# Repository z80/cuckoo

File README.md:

# Micropython Board
A convenient to work with implementation. It is not a minimalistic design, 
it has a full size USB-B socket, 16Mb of external SPI memory. The board is driven by STM32 microcontroller STM32F405RGT6.

All min arrays have extensive ground shielding and even neighbor pins have minimal crosstalk.

The layout is designed closely following the rules made by Hans Rosenberg, shared in his correct PCB layout tutorial videos.

# Audio Board
This is an extension for the micropython board. This audio board has a D-class on-chip power amplifier with analog input.

It has a step up 5V switching converter to ensure the audio driver is at 5V.

Also, it has a motion detector (PYR sensor) redinc circuit.

Lastly, it has a single driver circuit for an analog servo motor.

The intended usage of the board in Helloween props. The micropython board can be extended with this audio board to produce speech, detect when people approach, perform physical movements.

# Override Board
This board provides several analog and digital isolated IO channels. The intended use is to override analog turning axes in the Dial Sense Playstation 5 controller and force it to use external intertial aiming signal so that instead of being a torture device, it makes the Dual Sense to be pleasant to use.

# Servo Scull prop
A talking scull themed as Warhammer 40k Servo Scull by Adeptus Mechanicus.

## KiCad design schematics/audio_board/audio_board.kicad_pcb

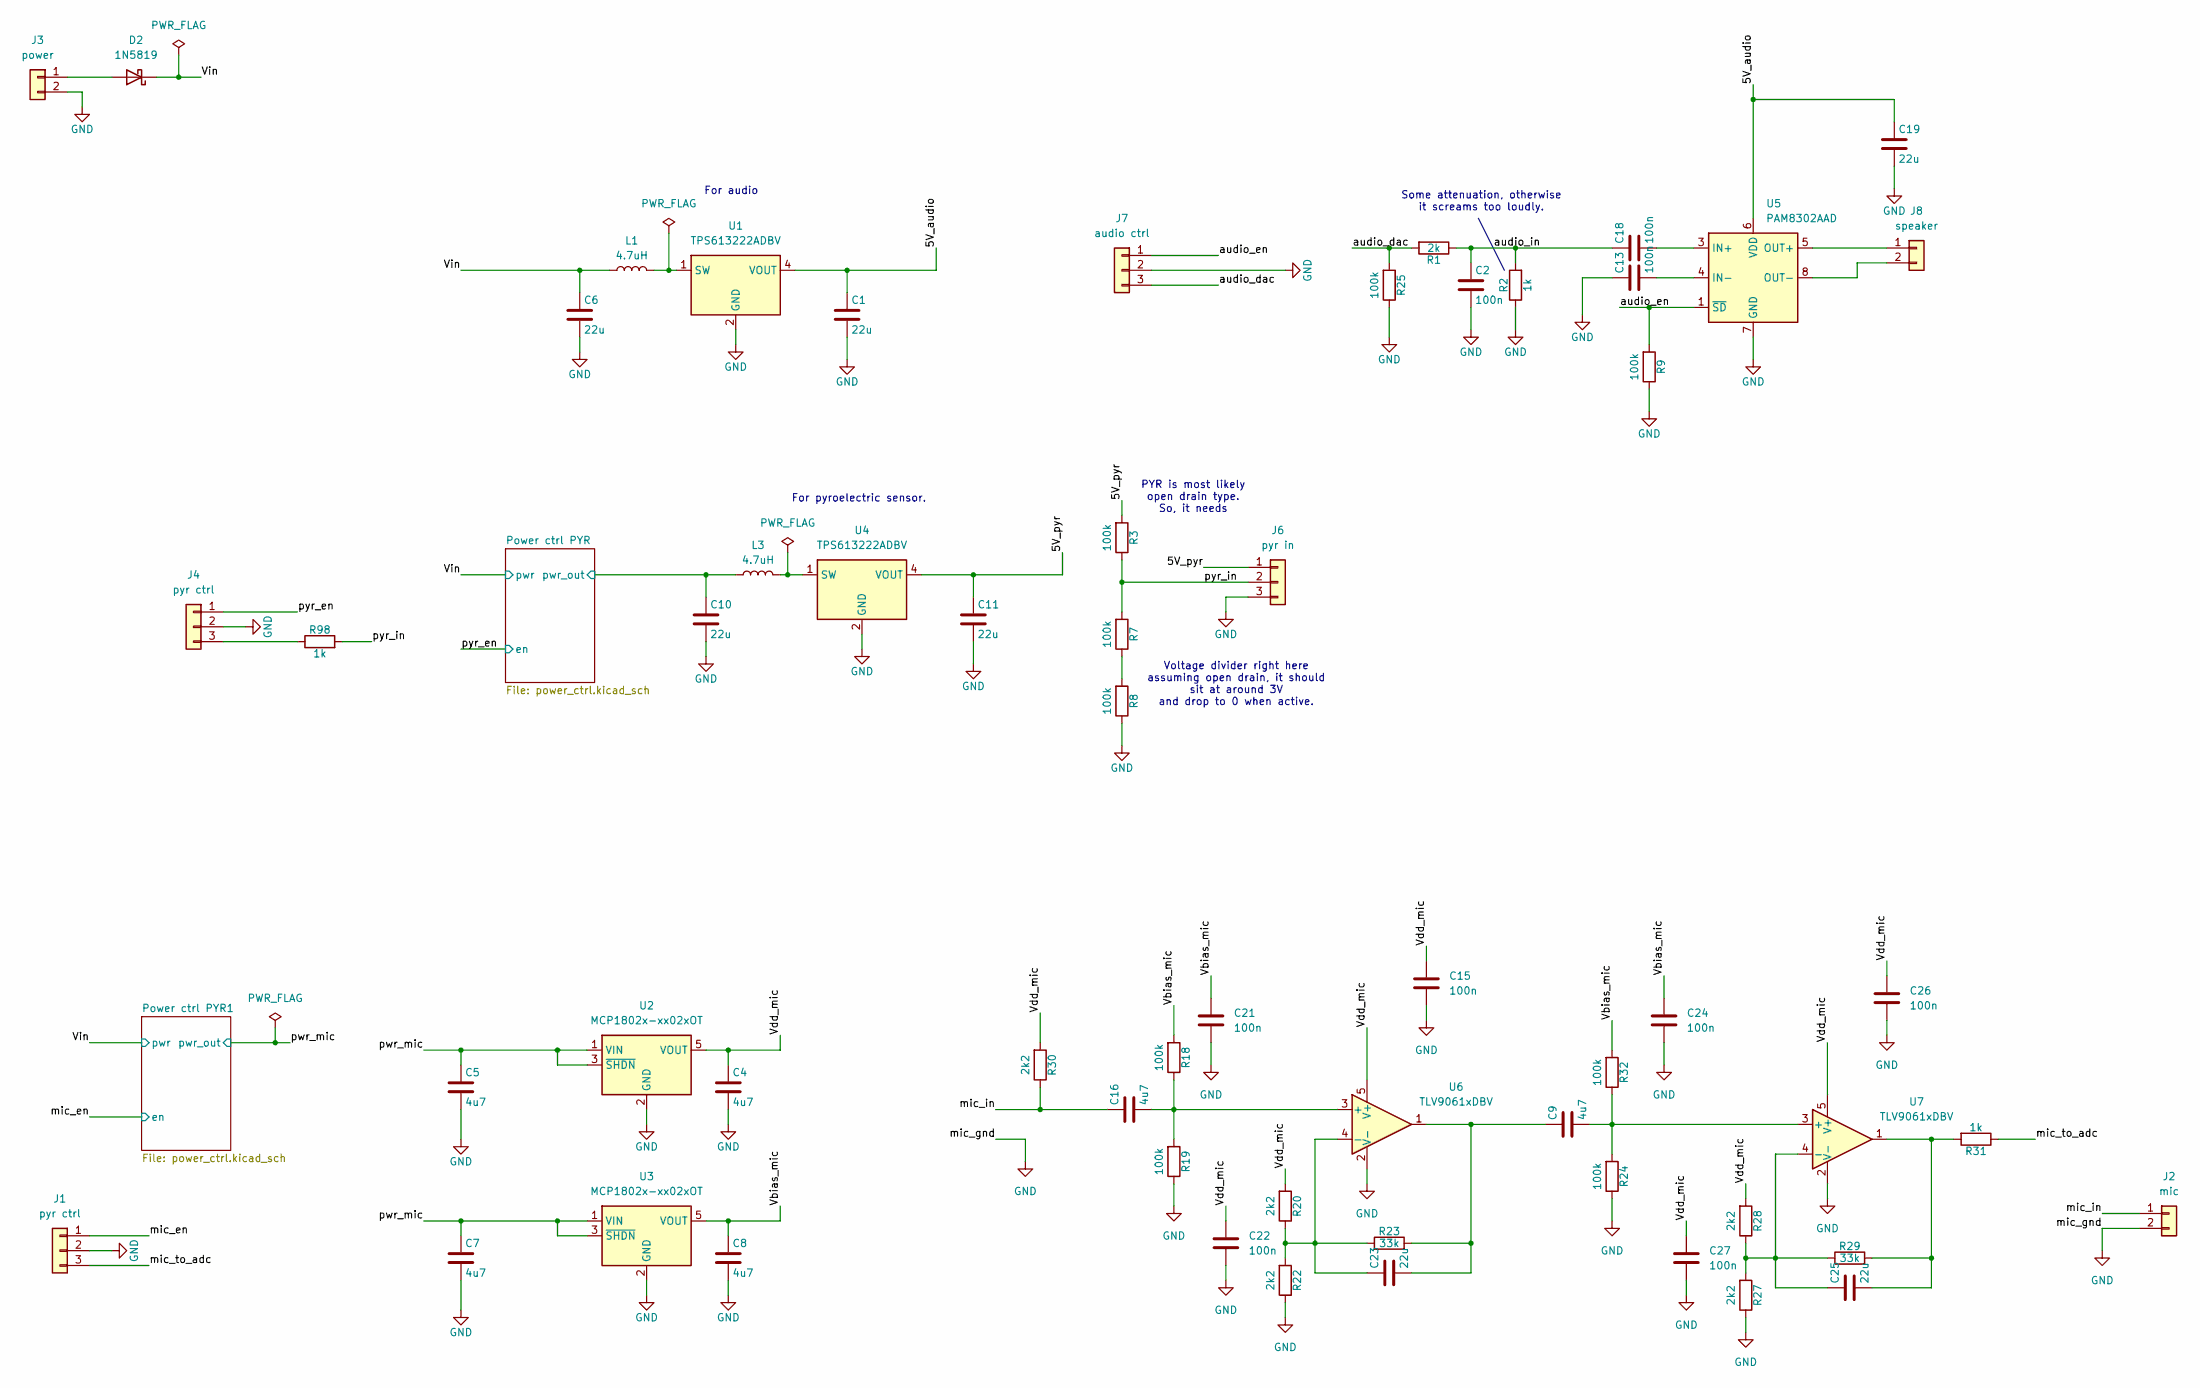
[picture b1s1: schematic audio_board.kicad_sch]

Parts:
C1, C6, C10, C11, C19, C23, C25: 22u; C_0603_1608Metric_Pad1.08x0.95mm_HandSolder
C2, C13, C18: 100n; C_0603_1608Metric_Pad1.08x0.95mm_HandSolder
C4, C5, C7, C8, C9, C16: 4u7; C_0603_1608Metric
C15, C21, C22, C24, C26, C27: 100n; C_0603_1608Metric
D2: 1N5819; D_DO-41_SOD81_P7.62mm_Horizontal
J1, J4: pyr ctrl; PinSocket_1x03_P2.54mm_Vertical
J2: mic; PinSocket_1x02_P2.54mm_Vertical
J3: power; PinSocket_1x02_P2.54mm_Vertical
J6: pyr in; PinSocket_1x03_P2.54mm_Vertical
J7: audio ctrl; PinSocket_1x03_P2.54mm_Vertical
J8: speaker; PinSocket_1x02_P2.54mm_Vertical
L1, L3: 4.7uH; L_1008_2520Metric
R1: 2k; C_0603_1608Metric_Pad1.08x0.95mm_HandSolder
R2, R31, R98: 1k; C_0603_1608Metric_Pad1.08x0.95mm_HandSolder
R3, R7, R8, R9, R18, R19, R24, R25, R32: 100k; R_0603_1608Metric_Pad0.98x0.95mm_HandSolder
R20, R22, R27, R28, R30: 2k2; R_0603_1608Metric_Pad0.98x0.95mm_HandSolder
R23, R29: 33k; C_0603_1608Metric_Pad1.08x0.95mm_HandSolder
U1, U4: TPS613222ADBV; SOT-23-5
U2, U3: MCP1802x-xx02xOT; SOT-23-5
U5: PAM8302AAD; MSOP-8_3x3mm_P0.65mm
U6, U7: TLV9061xDBV; SOT-23-5

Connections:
/5V_audio: C1.1, C19.1, U1.4 (VOUT), U5.6 (VDD)
/5V_pyr: C11.1, J6.1, R3.2, U4.4 (VOUT)
/Power ctrl PYR/pwr_out: C10.1, L3.1; also elsewhere on the board
/Vbias_mic: C8.1, C21.1, C24.1, R18.2, R32.2, U3.5 (VOUT)
/Vdd_mic: C4.1, C15.1, C22.1, C26.1, C27.1, R20.2, R28.2, R30.2, U2.5 (VOUT), U6.5 (V+), U7.5 (V+)
/Vin: C6.1, D2.1 (K), L1.1; also elsewhere on the board
/audio_dac: J7.3, R1.2, R25.2
/audio_en: J7.1, R9.2, U5.1 (~SD)
/audio_in: C2.1, C18.1, R1.1, R2.2
/mic_en: J1.1; also elsewhere on the board
/mic_in: C16.1, J2.1, R30.1
/mic_to_adc: J1.3, R31.1
/pwr_mic: C5.1, C7.1, U2.1 (VIN), U2.3 (~SHDN), U3.1 (VIN), U3.3 (~SHDN); also elsewhere on the board
/pyr_en: J4.1; also elsewhere on the board
/pyr_in: J6.2, R3.1, R7.2, R98.2
GND: C1.2, C2.2, C4.2, C5.2, C6.2, C7.2, C8.2, C10.2, C11.2, C13.1, C15.2, C19.2, C21.2, C22.2, C24.2, C26.2, C27.2, J1.2, J2.2, J3.2, J4.2, J6.3, J7.2, R2.1, R8.1, R9.1, R19.1, R22.1, R24.1, R25.1, R27.1, U1.2 (GND), U2.2 (GND), U3.2 (GND), U4.2 (GND), U5.7 (GND), U6.2 (V-), U7.2 (V-); also elsewhere on the board
unnamed: C9.1, C23.2, R23.2, U6.1
unnamed: C25.2, R29.2, R31.2, U7.1
unnamed: D2.2 (A), J3.1
unnamed: J4.3, R98.1
unnamed: J8.1, U5.5 (OUT+)
unnamed: J8.2, U5.8 (OUT-)
unnamed: R7.1, R8.2
unnamed: L1.2, U1.1 (SW)
unnamed: L3.2, U4.1 (SW)
unnamed: C18.2, U5.3 (IN+)
unnamed: C13.2, U5.4 (IN-)
unnamed: C16.2, R18.1, R19.2, U6.3 (+)
unnamed: C23.1, R20.1, R22.2, R23.1, U6.4 (-)
unnamed: C9.2, R24.2, R32.1, U7.3 (+)
unnamed: C25.1, R27.2, R28.1, R29.1, U7.4 (-)

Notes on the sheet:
For pyroelectric sensor.
PYR is most likely open drain type. So, it needs
For audio
Voltage divider right here assuming open drain, it should sit at around 3V and drop to 0 when active.
Some attenuation, otherwise it screams too loudly.

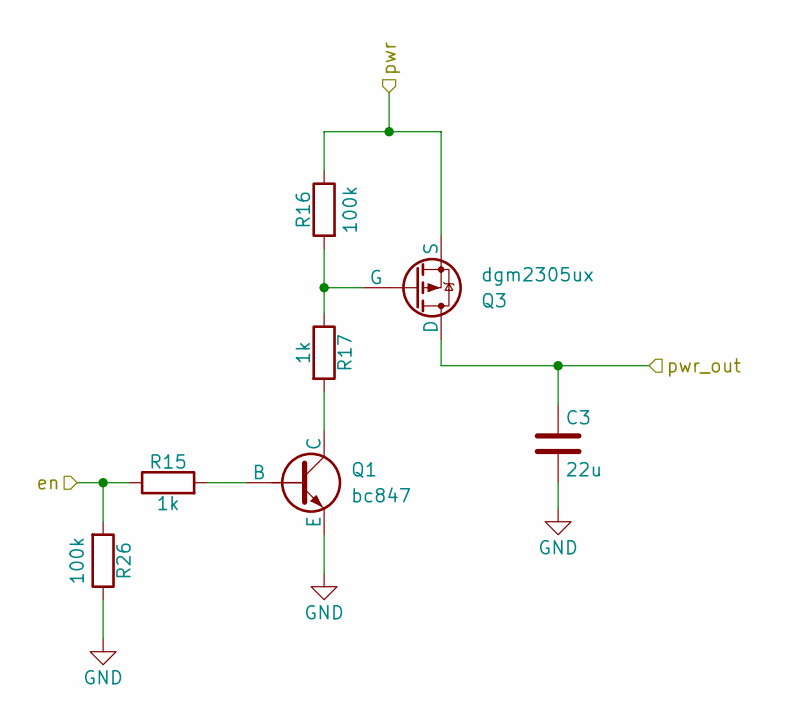
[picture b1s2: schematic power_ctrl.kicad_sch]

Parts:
C3: 22u; C_0603_1608Metric_Pad1.08x0.95mm_HandSolder
Q1: bc847; SOT-23
Q3: dgm2305ux; SOT-23
R15, R17: 1k; C_0603_1608Metric_Pad1.08x0.95mm_HandSolder
R16, R26: 100k; R_0603_1608Metric_Pad0.98x0.95mm_HandSolder

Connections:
/Vin: Q3.2 (S), R16.1; also elsewhere on the board
/mic_en: R15.1, R26.2; also elsewhere on the board
/pwr_mic: C3.1, Q3.3 (D); also elsewhere on the board
GND: C3.2, Q1.2 (E), R26.1; also elsewhere on the board
unnamed: Q1.1 (B), R15.2
unnamed: Q1.3 (C), R17.2
unnamed: Q3.1 (G), R16.2, R17.1

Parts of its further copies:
C14: 22u; C_0603_1608Metric_Pad1.08x0.95mm_HandSolder
Q2: bc847; SOT-23
Q7: dgm2305ux; SOT-23
R5, R11: 1k; C_0603_1608Metric_Pad1.08x0.95mm_HandSolder
R6, R33: 100k; R_0603_1608Metric_Pad0.98x0.95mm_HandSolder

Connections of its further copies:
/Power ctrl PYR/pwr_out: C14.1, Q7.3 (D); also elsewhere on the board
/Vin: Q7.2 (S), R6.1; also elsewhere on the board
/pyr_en: R5.1, R33.2; also elsewhere on the board
GND: C14.2, Q2.2 (E), R33.1; also elsewhere on the board
unnamed: Q2.1 (B), R5.2
unnamed: Q2.3 (C), R11.2
unnamed: Q7.1 (G), R6.2, R11.1

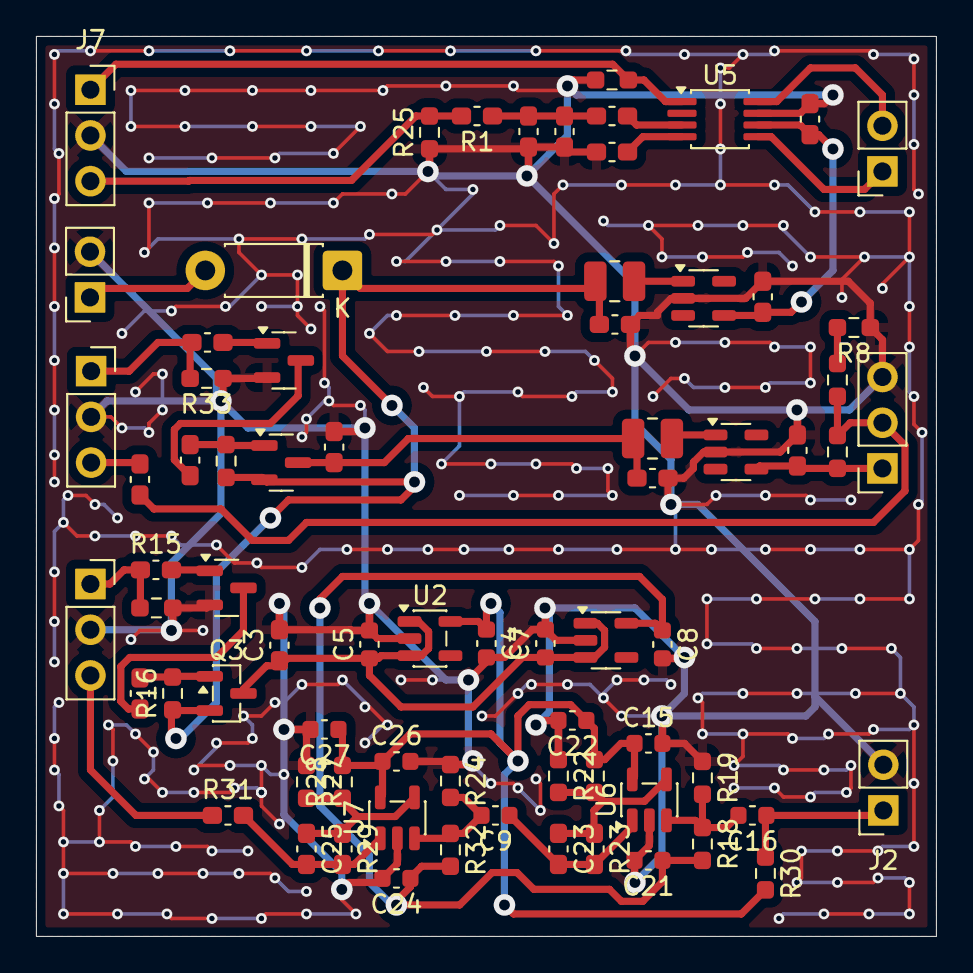
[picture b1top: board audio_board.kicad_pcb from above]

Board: 2 copper layers, 50.0 x 50.0 mm, 73 parts (0 on the bottom side), 37 nets.

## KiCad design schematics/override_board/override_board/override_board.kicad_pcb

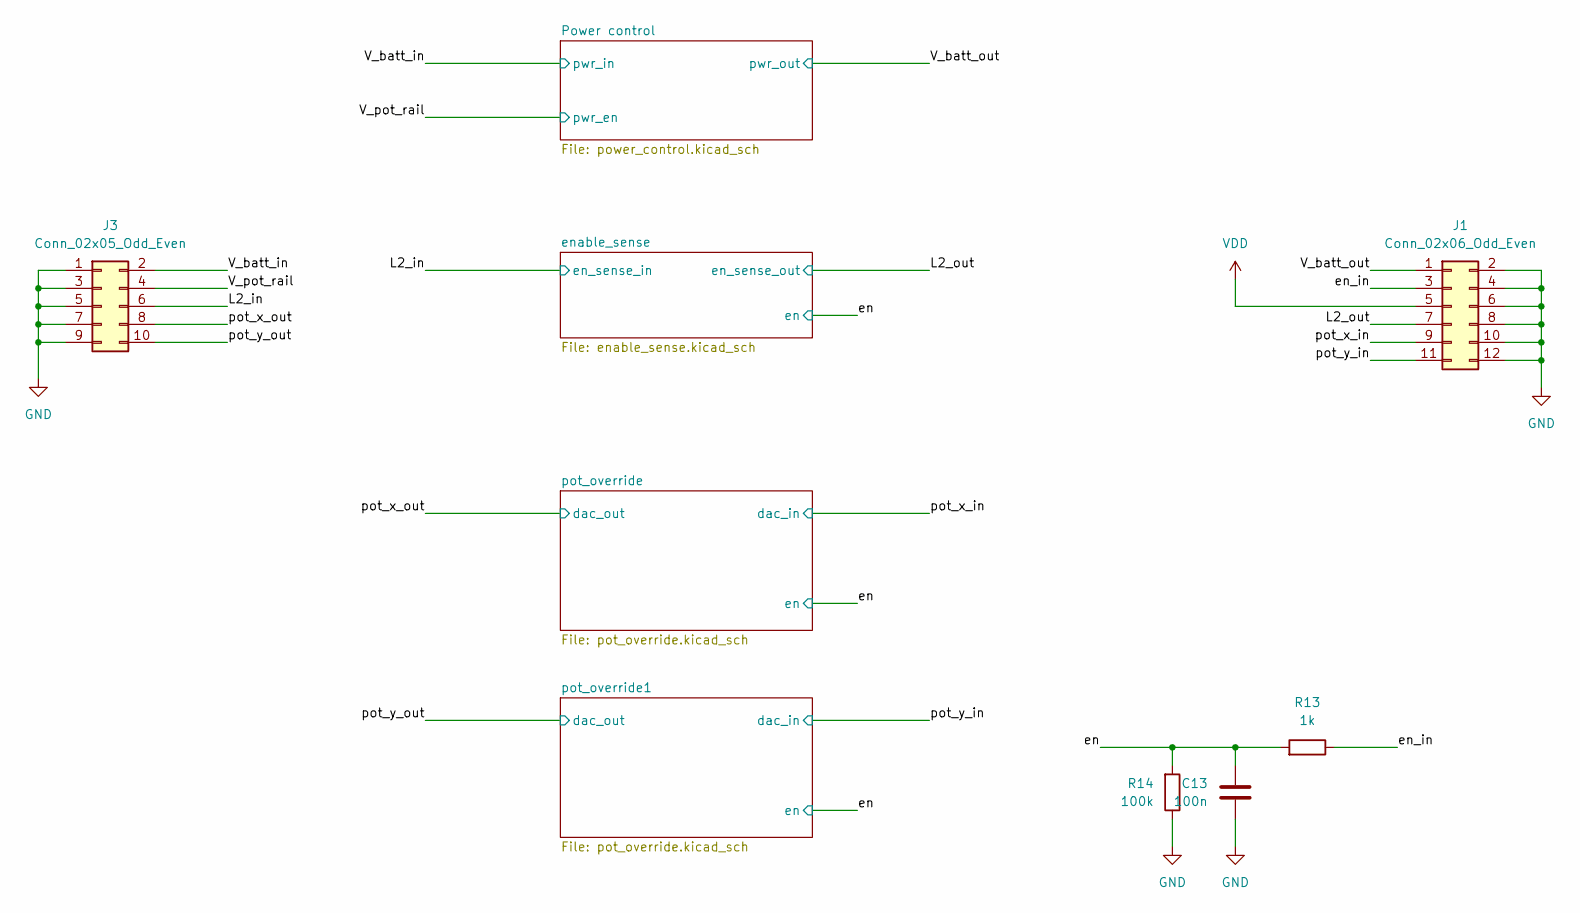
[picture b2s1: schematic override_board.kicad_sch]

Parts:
C13: 100n; C_0603_1608Metric
J1: Conn_02x06_Odd_Even; PinHeader_2x06_P2.54mm_Vertical
J3: Conn_02x05_Odd_Even; PinHeader_2x05_P2.54mm_Vertical
R13: 1k; R_0603_1608Metric
R14: 100k; R_0603_1608Metric

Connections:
/L2_in: J3.6; also elsewhere on the board
/L2_out: J1.7; also elsewhere on the board
/V_batt_in: J3.2; also elsewhere on the board
/V_batt_out: J1.1; also elsewhere on the board
/V_pot_rail: J3.4; also elsewhere on the board
/en: C13.1, R13.2, R14.2; also elsewhere on the board
/en_in: J1.3, R13.1
/pot_x_in: J1.9; also elsewhere on the board
/pot_x_out: J3.8; also elsewhere on the board
/pot_y_in: J1.11; also elsewhere on the board
/pot_y_out: J3.10; also elsewhere on the board
GND: C13.2, J1.2, J1.4, J1.6, J1.8, J1.10, J1.12, J3.1, J3.3, J3.5, J3.7, J3.9, R14.1; also elsewhere on the board
VDD: J1.5; also elsewhere on the board

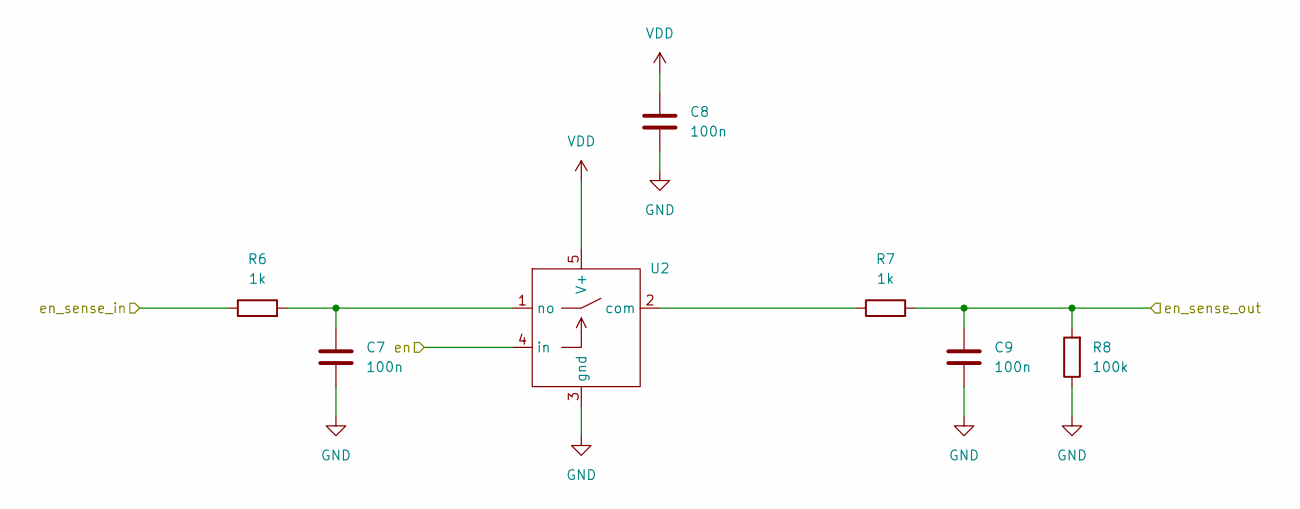
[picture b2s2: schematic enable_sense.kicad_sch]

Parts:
C7, C8, C9: 100n; C_0603_1608Metric
R6, R7: 1k; R_0603_1608Metric
R8: 100k; R_0603_1608Metric
U2: SOT-23-5

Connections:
/L2_in: R6.1; also elsewhere on the board
/L2_out: C9.1, R7.2, R8.2; also elsewhere on the board
/en: U2.4 (in); also elsewhere on the board
GND: C7.2, C8.2, C9.2, R8.1, U2.3 (gnd); also elsewhere on the board
unnamed: R7.1, U2.2 (com)
unnamed: C7.1, R6.2, U2.1 (no)
VDD: C8.1, U2.5 (V+); also elsewhere on the board

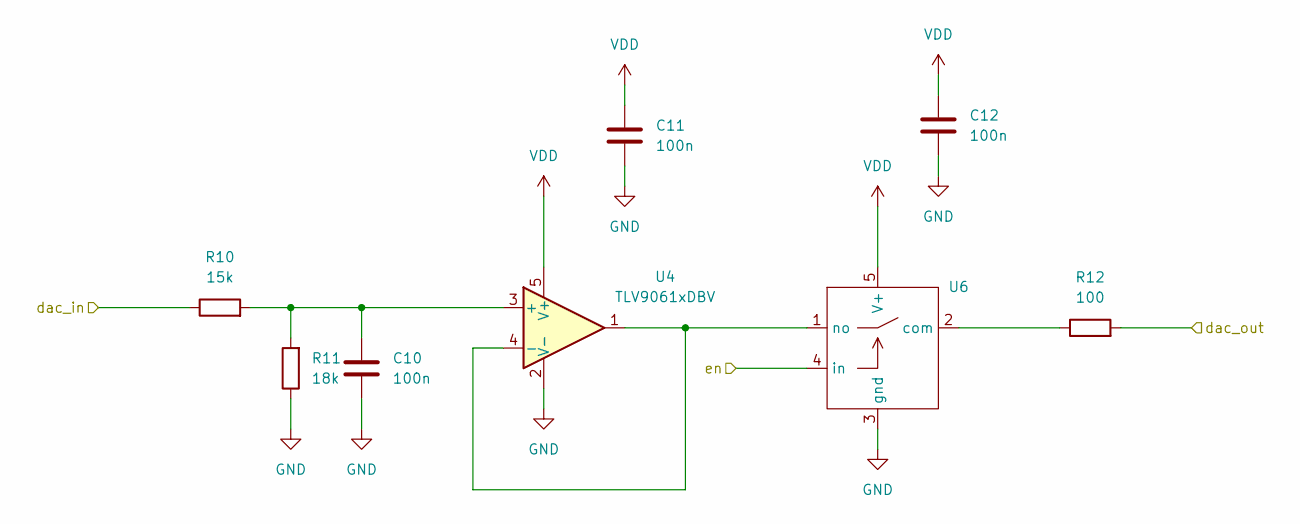
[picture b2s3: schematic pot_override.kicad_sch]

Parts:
C10, C11, C12: 100n; C_0603_1608Metric
R10: 15k; R_0603_1608Metric
R11: 18k; R_0603_1608Metric
R12: 100; R_0603_1608Metric
U4: TLV9061xDBV; SOT-23-5
U6: SOT-23-5

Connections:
/en: U6.4 (in); also elsewhere on the board
/pot_x_in: R10.1; also elsewhere on the board
/pot_x_out: R12.2; also elsewhere on the board
GND: C10.2, C11.2, C12.2, R11.1, U4.2 (V-), U6.3 (gnd); also elsewhere on the board
unnamed: C10.1, R10.2, R11.2, U4.3 (+)
unnamed: U4.1, U4.4 (-), U6.1 (no)
unnamed: R12.1, U6.2 (com)
VDD: C11.1, C12.1, U4.5 (V+), U6.5 (V+); also elsewhere on the board

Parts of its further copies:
C4, C5, C6: 100n; C_0603_1608Metric
R3: 15k; R_0603_1608Metric
R4: 18k; R_0603_1608Metric
R5: 100; R_0603_1608Metric
U3: TLV9061xDBV; SOT-23-5
U5: SOT-23-5

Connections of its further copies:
/en: U5.4 (in); also elsewhere on the board
/pot_y_in: R3.1; also elsewhere on the board
/pot_y_out: R5.2; also elsewhere on the board
GND: C4.2, C5.2, C6.2, R4.1, U3.2 (V-), U5.3 (gnd); also elsewhere on the board
unnamed: C4.1, R3.2, R4.2, U3.3 (+)
unnamed: U3.1, U3.4 (-), U5.1 (no)
unnamed: R5.1, U5.2 (com)
VDD: C5.1, C6.1, U3.5 (V+), U5.5 (V+); also elsewhere on the board

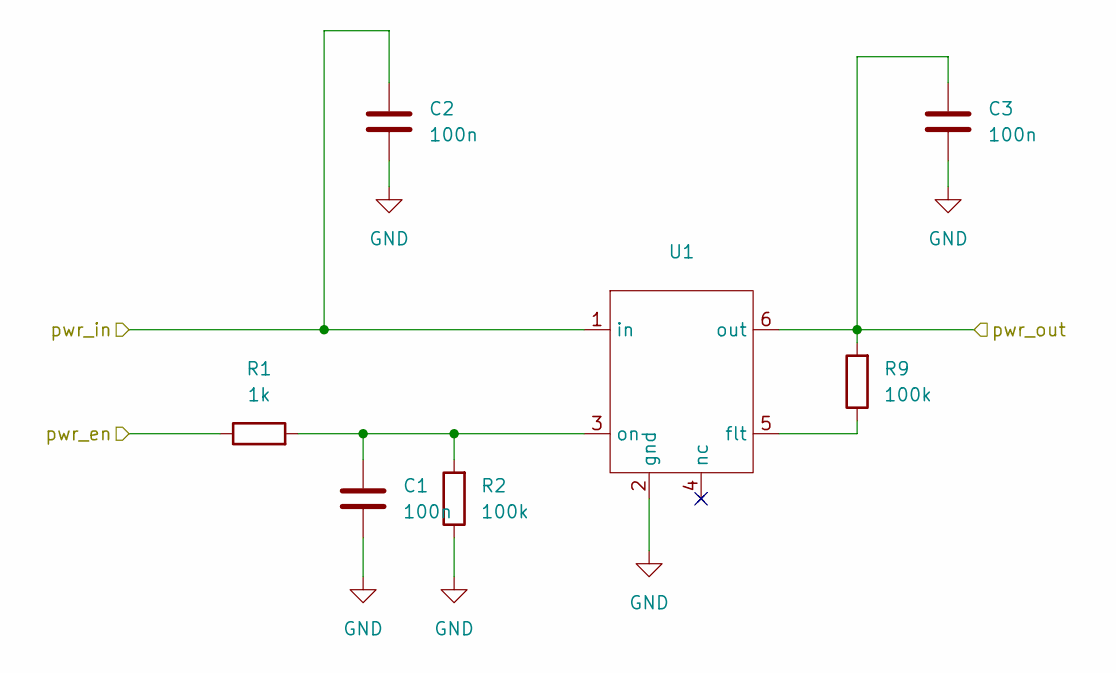
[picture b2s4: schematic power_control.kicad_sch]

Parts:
C1, C2, C3: 100n; C_0603_1608Metric
R1: 1k; R_0603_1608Metric
R2, R9: 100k; R_0603_1608Metric
U1: SOT-363_SC-70-6

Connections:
/V_batt_in: C2.1, U1.1 (in); also elsewhere on the board
/V_batt_out: C3.1, R9.2, U1.6 (out); also elsewhere on the board
/V_pot_rail: R1.1; also elsewhere on the board
GND: C1.2, C2.2, C3.2, R2.1, U1.2 (gnd); also elsewhere on the board
unnamed: R9.1, U1.5 (flt)
unnamed: C1.1, R1.2, R2.2, U1.3 (on)

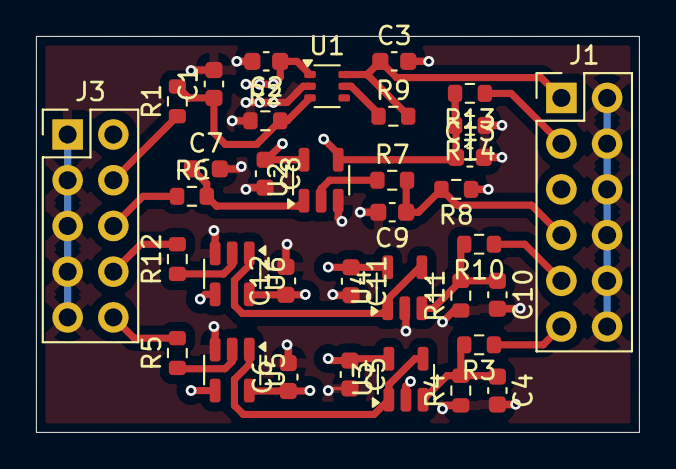
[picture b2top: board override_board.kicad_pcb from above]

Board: 4 copper layers, 33.5 x 22.0 mm, 35 parts (0 on the bottom side), 23 nets.

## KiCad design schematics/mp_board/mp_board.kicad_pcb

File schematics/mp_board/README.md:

A custom MicroPython-based Stm32 board with integrated Flash memory.

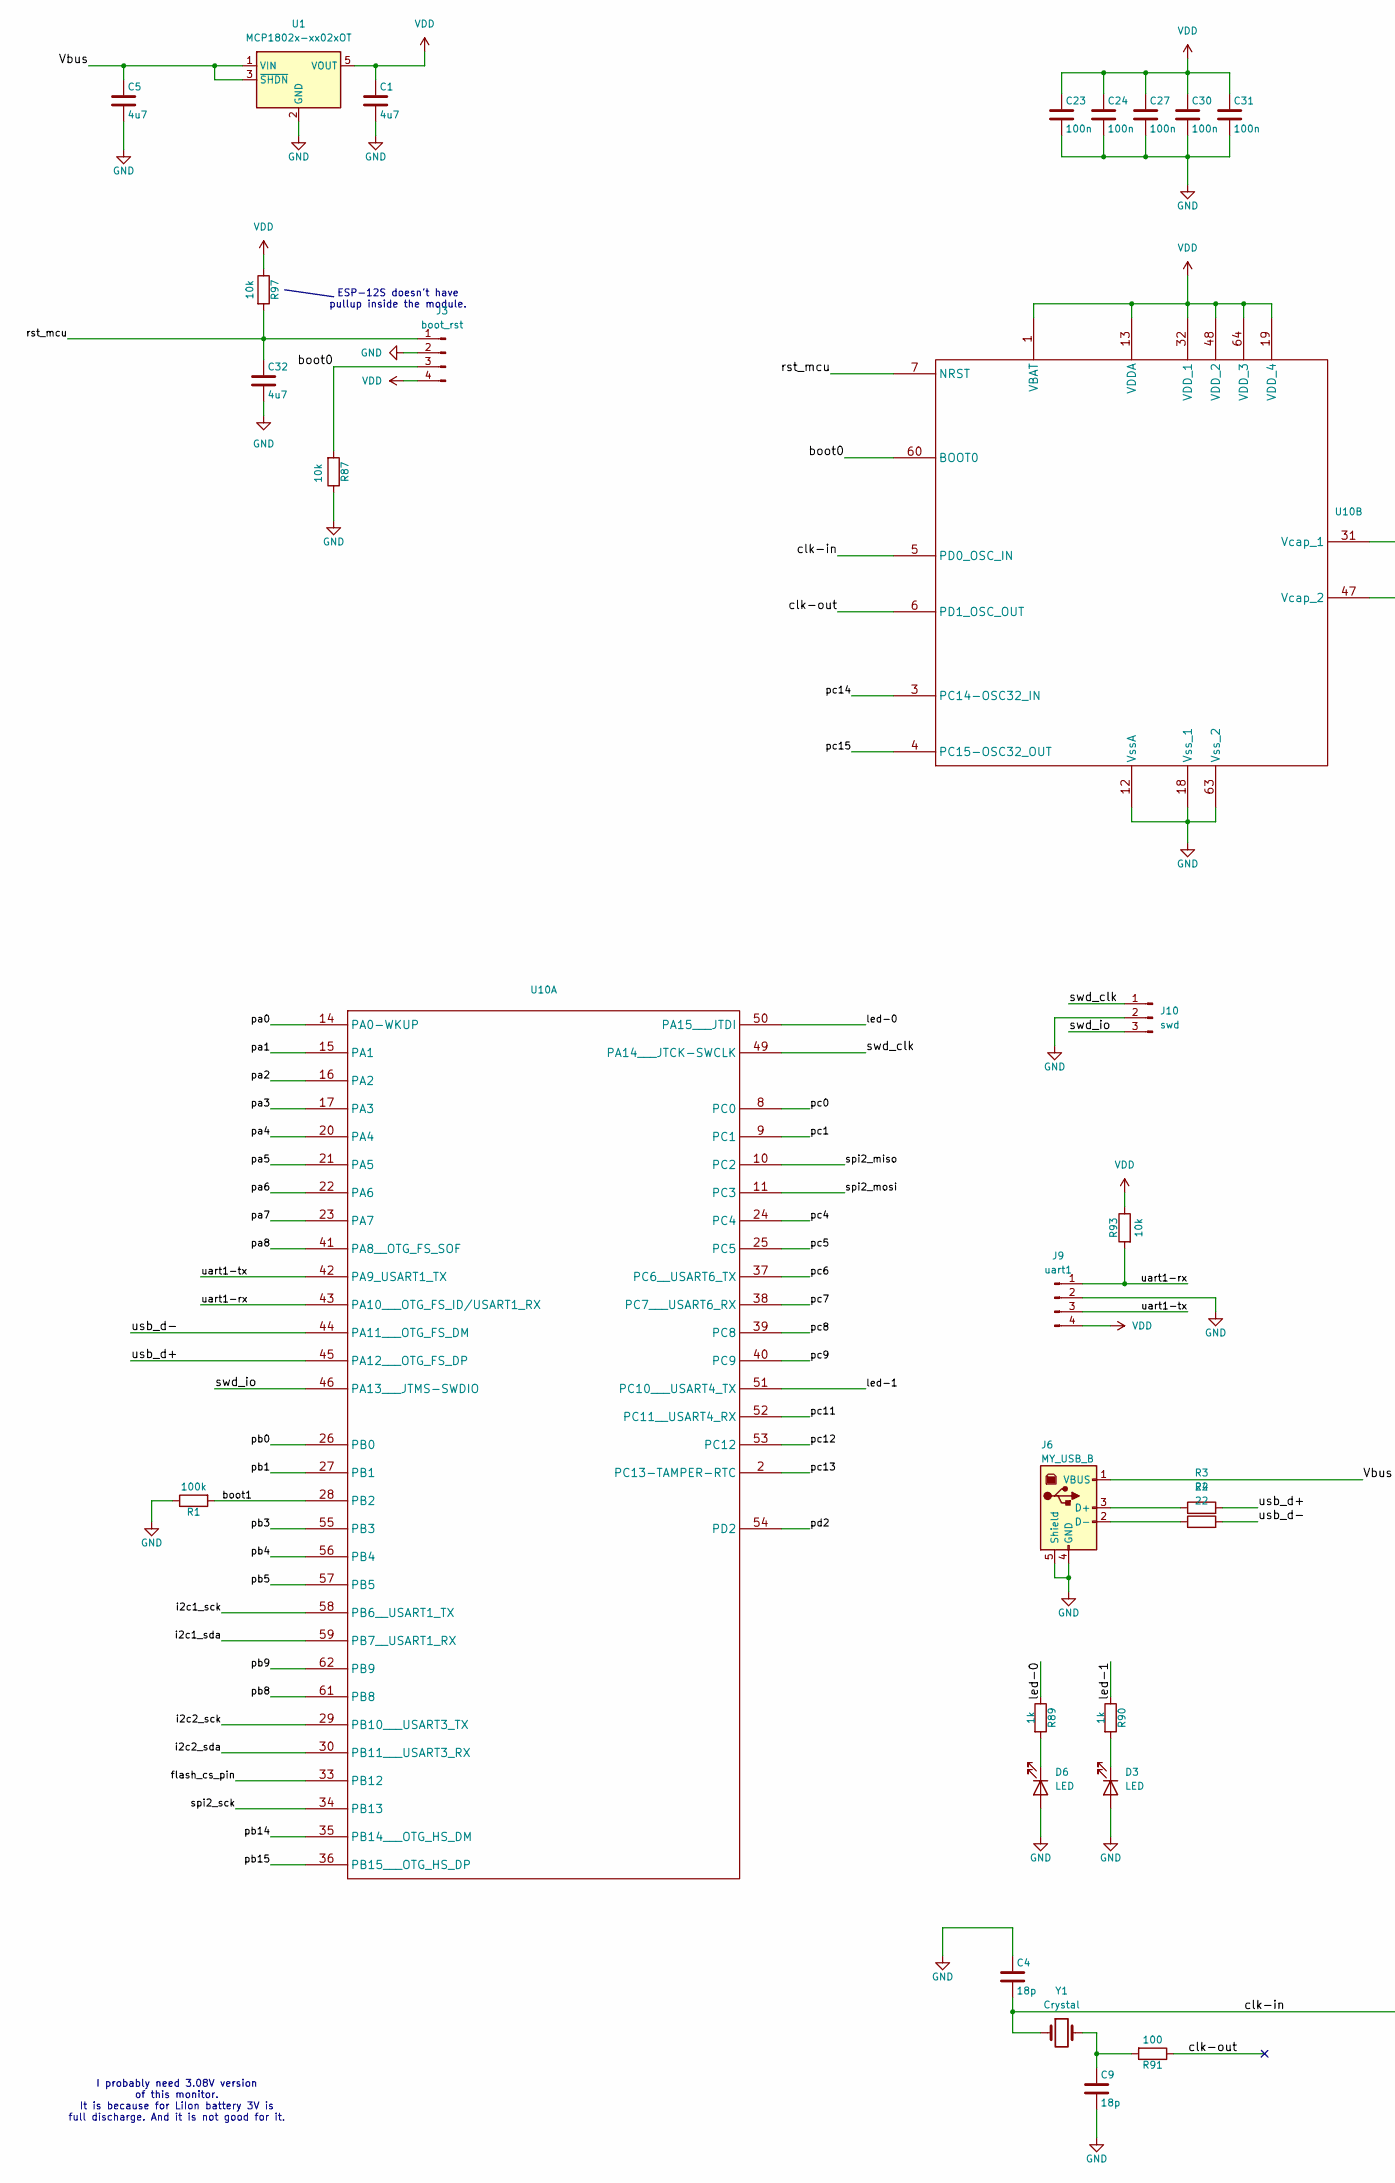
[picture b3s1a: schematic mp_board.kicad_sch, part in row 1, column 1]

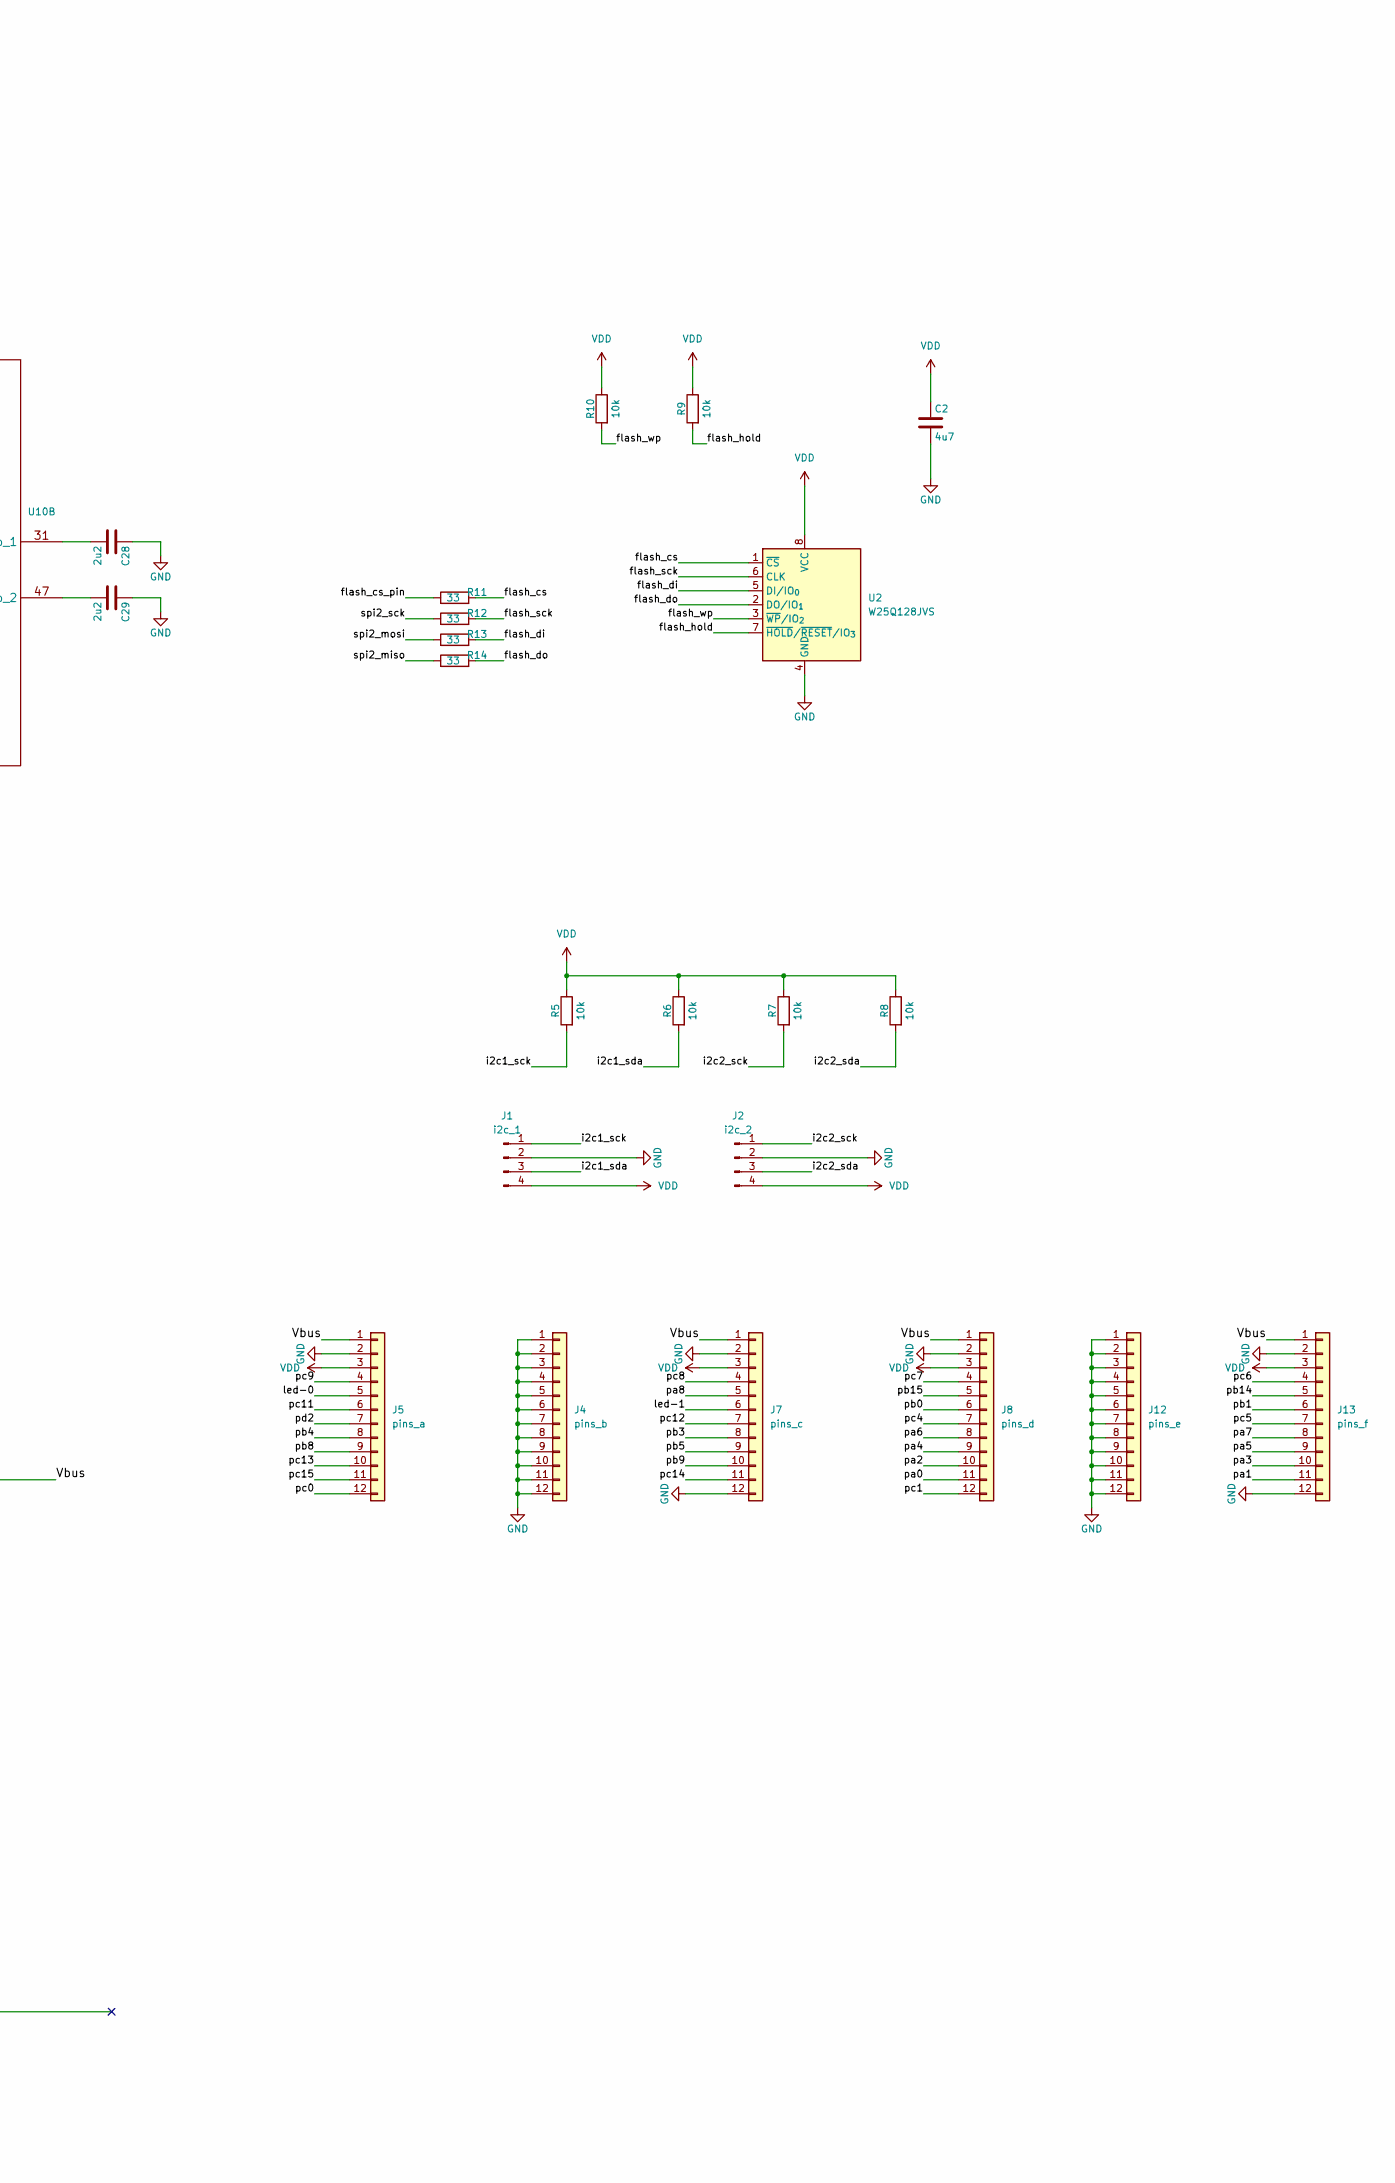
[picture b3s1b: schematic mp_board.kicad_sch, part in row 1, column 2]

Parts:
C1, C2, C5, C32: 4u7; C_0603_1608Metric
C4, C9: 18p; C_0603_1608Metric
C23, C24, C27, C30, C31: 100n; C_0603_1608Metric
C28, C29: 2u2; C_0603_1608Metric
D3, D6: LED; LED_D3.0mm
J1: i2c_1; PinHeader_1x04_P2.54mm_Vertical
J2: i2c_2; PinHeader_1x04_P2.54mm_Vertical
J3: boot_rst; PinHeader_1x04_P2.54mm_Vertical
J4: pins_b; PinHeader_1x12_P2.54mm_Vertical
J5: pins_a; PinHeader_1x12_P2.54mm_Vertical
J6: MY_USB_B; USB_B_Lumberg_2411_02_Horizontal
J7: pins_c; PinHeader_1x12_P2.54mm_Vertical
J8: pins_d; PinHeader_1x12_P2.54mm_Vertical
J9: uart1; PinHeader_1x04_P2.54mm_Vertical
J10: swd; PinHeader_1x03_P2.54mm_Vertical
J12: pins_e; PinHeader_1x12_P2.54mm_Vertical
J13: pins_f; PinHeader_1x12_P2.54mm_Vertical
R1: 100k; R_0603_1608Metric
R3, R4: 22; R_0603_1608Metric
R5, R6, R7, R8, R9, R10, R87, R93: 10k; R_0603_1608Metric
R11, R12, R13, R14: 33; R_0603_1608Metric_Pad0.98x0.95mm_HandSolder
R89, R90: 1k; R_0603_1608Metric
R91: 100; R_0603_1608Metric
R97: 10k; C_0603_1608Metric
U1: MCP1802x-xx02xOT; SOT-23-5
U2: W25Q128JVS; SOIC-8_5.3x5.3mm_P1.27mm
U10: LQFP-64_10x10mm_P0.5mm
Y1: Crystal; Crystal_HC52-8mm_Vertical

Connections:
/Vbus: C5.1, J5.1, J6.1 (VBUS), J7.1, J8.1, J13.1, U1.1 (VIN), U1.3 (~SHDN)
/boot0: J3.3, R87.2, U10.60 (BOOT0)
/boot1: R1.2, U10.28 (PB2)
/clk-in: C4.2, U10.5 (PD0_OSC_IN), Y1.1
/clk-out: R91.1, U10.6 (PD1_OSC_OUT)
/flash_cs: R11.2, U2.1 (~CS)
/flash_cs_pin: R11.1, U10.33 (PB12)
/flash_di: R13.2, U2.5 (DI/IO_{0})
/flash_do: R14.2, U2.2 (DO/IO_{1})
/flash_hold: R9.2, U2.7 (~HOLD/~RESET/IO_{3})
/flash_sck: R12.2, U2.6 (CLK)
/flash_wp: R10.2, U2.3 (~WP/IO_{2})
/i2c1_sck: J1.1, R5.2, U10.58 (PB6__USART1_TX)
/i2c1_sda: J1.3, R6.2, U10.59 (PB7__USART1_RX)
/i2c2_sck: J2.1, R7.2, U10.29 (PB10___USART3_TX)
/i2c2_sda: J2.3, R8.2, U10.30 (PB11___USART3_RX)
/led-0: J5.5, R89.1, U10.50 (PA15___JTDI)
/led-1: J7.6, R90.1, U10.51 (PC10___USART4_TX)
/pa0: J8.11, U10.14 (PA0-WKUP)
/pa1: J13.11, U10.15 (PA1)
/pa2: J8.10, U10.16 (PA2)
/pa3: J13.10, U10.17 (PA3)
/pa4: J8.9, U10.20 (PA4)
/pa5: J13.9, U10.21 (PA5)
/pa6: J8.8, U10.22 (PA6)
/pa7: J13.8, U10.23 (PA7)
/pa8: J7.5, U10.41 (PA8__OTG_FS_SOF)
/pb0: J8.6, U10.26 (PB0)
/pb1: J13.6, U10.27 (PB1)
/pb3: J7.8, U10.55 (PB3)
/pb4: J5.8, U10.56 (PB4)
/pb5: J7.9, U10.57 (PB5)
/pb8: J5.9, U10.61 (PB8)
/pb9: J7.10, U10.62 (PB9)
/pb14: J13.5, U10.35 (PB14___OTG_HS_DM)
/pb15: J8.5, U10.36 (PB15___OTG_HS_DP)
/pc0: J5.12, U10.8 (PC0)
/pc1: J8.12, U10.9 (PC1)
/pc4: J8.7, U10.24 (PC4)
/pc5: J13.7, U10.25 (PC5)
/pc6: J13.4, U10.37 (PC6__USART6_TX)
/pc7: J8.4, U10.38 (PC7___USART6_RX)
/pc8: J7.4, U10.39 (PC8)
/pc9: J5.4, U10.40 (PC9)
/pc11: J5.6, U10.52 (PC11__USART4_RX)
/pc12: J7.7, U10.53 (PC12)
/pc13: J5.10, U10.2 (PC13-TAMPER-RTC)
/pc14: J7.11, U10.3 (PC14-OSC32_IN)
/pc15: J5.11, U10.4 (PC15-OSC32_OUT)
/pd2: J5.7, U10.54 (PD2)
/rst_mcu: C32.1, J3.1, R97.2, U10.7 (NRST)
/spi2_miso: R14.1, U10.10 (PC2)
/spi2_mosi: R13.1, U10.11 (PC3)
/spi2_sck: R12.1, U10.34 (PB13)
/swd_clk: J10.1, U10.49 (PA14___JTCK-SWCLK)
/swd_io: J10.3, U10.46 (PA13___JTMS-SWDIO)
/uart1-rx: J9.1, R93.2, U10.43 (PA10___OTG_FS_ID/USART1_RX)
/uart1-tx: J9.3, U10.42 (PA9_USART1_TX)
/usb_d+: R3.2, U10.45 (PA12___OTG_FS_DP)
/usb_d-: R4.2, U10.44 (PA11___OTG_FS_DM)
GND: C1.2, C2.2, C4.1, C5.2, C9.2, C23.2, C24.2, C27.2, C28.1, C29.1, C30.2, C31.2, C32.2, D3.2 (A), D6.2 (A), J1.2, J2.2, J3.2, J4.1, J4.2, J4.3, J4.4, J4.5, J4.6, J4.7, J4.8, J4.9, J4.10, J4.11, J4.12, J5.2, J6.4 (GND), J6.5 (Shield), J7.2, J7.12, J8.2, J9.2, J10.2, J12.1, J12.2, J12.3, J12.4, J12.5, J12.6, J12.7, J12.8, J12.9, J12.10, J12.11, J12.12, J13.2, J13.12, R1.1, R87.1, U1.2 (GND), U2.4 (GND), U10.12 (VssA), U10.18 (Vss_1), U10.63 (Vss_2)
unnamed: C9.1, R91.2, Y1.2
unnamed: D3.1 (K), R90.2
unnamed: D6.1 (K), R89.2
unnamed: J6.3 (D+), R3.1
unnamed: J6.2 (D-), R4.1
unnamed: C28.2, U10.31 (Vcap_1)
unnamed: C29.2, U10.47 (Vcap_2)
VDD: C1.1, C2.1, C23.1, C24.1, C27.1, C30.1, C31.1, J1.4, J2.4, J3.4, J5.3, J7.3, J8.3, J9.4, J13.3, R5.1, R6.1, R7.1, R8.1, R9.1, R10.1, R93.1, R97.1, U1.5 (VOUT), U2.8 (VCC), U10.1 (VBAT), U10.13 (VDDA), U10.19 (VDD_4), U10.32 (VDD_1), U10.48 (VDD_2), U10.64 (VDD_3)

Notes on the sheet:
I probably need 3.08V version of this monitor. It is because for LiIon battery 3V is full discharge. And it is not good for it.
ESP-12S doesn't have pullup inside the module.

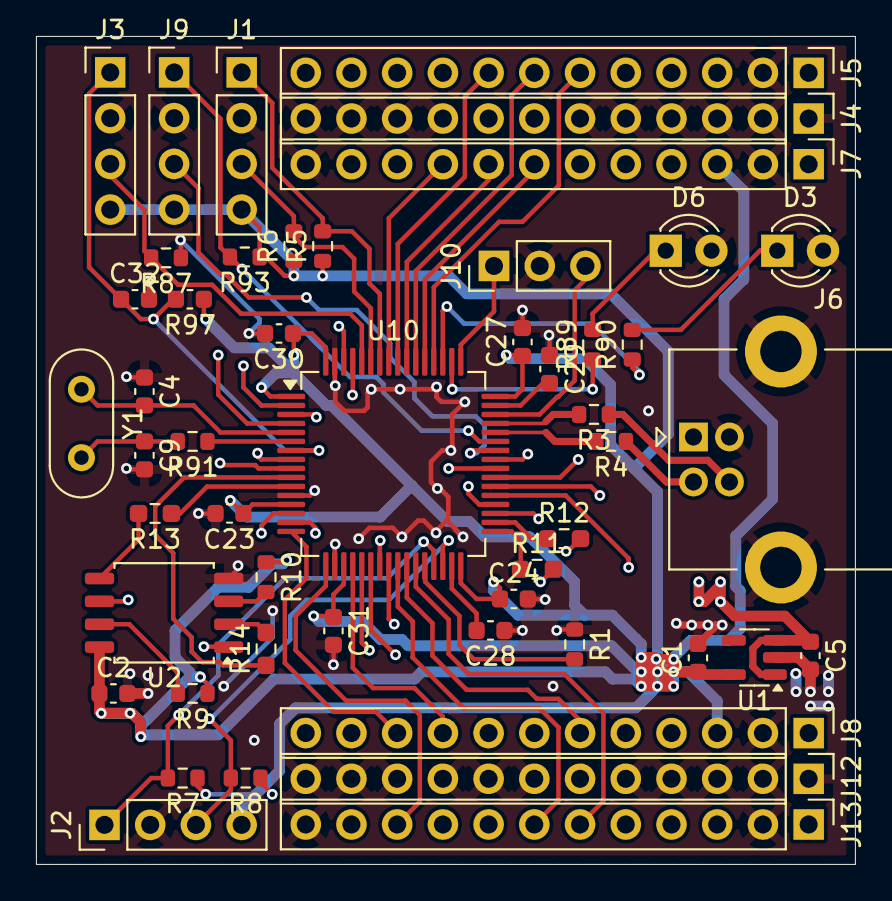
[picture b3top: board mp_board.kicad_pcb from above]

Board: 4 copper layers, 45.5 x 46.0 mm, 50 parts (0 on the bottom side), 69 nets.
